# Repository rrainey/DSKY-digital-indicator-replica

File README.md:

# DSKY Digital Panel Replica

This is a scale functional replica of the Digital Indicator panel for the Apollo Guidance Computer. It is
designed to be part of a larger replica of the Display and Keyboard (DSKY) module of the AGC.

This project is composed of these component subfolders:

* **artwork** - artwork to be printed or silk-screened onto the glass/acrylic cover.

* **pcb** - KiCad 9 project for the controller PCB design.

* **firmware** - Arduino-based controller firmware.  This module is designed to be controlled via the USB serial interface.

* **hardware** - 3D-printable frame components designed using Fusion 360. STEP and Fusion source files available. Hardware models used in thie replica were derived from models that are part of in the [AGC Mechanical CAD project](https://github.com/rrainey/agc-mechanical-cad).

## Bill of Materials

|  Part                   | Grainger Part |   MFR Part  | QTY | Description |
|------------------------|:---------------:|-------------|:-----:|-------------|
|  M2.5-0.45 Brass Insert| [1GNL7](https://www.grainger.com/product/Heat-Set-Insert-M2-5-0-45-1GNL7?searchQuery=1GNL7&searchBar=true) |  TH-M25-SV-PK100 | 4 | Brass inserts (sold as 100 pack) |
|  M2.5 x 6mm Screw      | [6HB66](https://www.grainger.com/product/Machine-Screw-M2-5-Thread-6HB66) |  MPFD025060-100P1 | 4 | Machine screw: M2.5 Thread Size, 6 mm Lg, Steel, Zinc Plated, Flat, Phillips, Metric (sold as 100 pack) |
| Body                   | - | - | 1 | 3D Printable part |
| Retainer               | - | - | 1 | 3D Printable part |
| Light Guide            | - | - | 1 | CNC or 3D Printable part |
| PCB to Light Guide Adapter | - | - | 1 | 3D Printable part |
| Indicator face         | - | - | 1 | Paper Printable part |

Models for all printable parts are located in the hardware subfolder.

## Interfaces

* USB 2.0 Micro-B port
* J-LINK-compatible SWD debugging interface (10-pin header)
* Power: +3.3VDC via a 4-pin header (2.1A maximum (estimated; software limited to 0.5A))

## Printed Circuit Board

Summary below. You will find more detailed notes in the [./pcb folder](./pcb/PCB-NOTES.md).

As of March 2025, V7 of the PCB design is current. Gerber and component placement files -- all generated by KiCad 7, are included in this repository.  [PCBWay](https://pcbway.com) generously sponsored this version of the project. If you are building one of these boards, you should consider them for either PCB fabrication or full-up PCB assembly.

I often use a solder reflow oven in my shop. I used PCBWay for full PCBA services on this latest version, but with the earlier boards - I assembled them myself using a [two step process](https://www.instructables.com/Making-double-side-boards-in-reflow-oven/) to first reflow the back (LED) side using Sn63/Pb37 paste, then reflow the front side using a lower temperature solder paste (Bi57Sn42Ag1).  

## Painting

The original NASA drawings for all variants of this component, [1006387D for example,](https://archive.org/stream/apertureCardBox439Part2NARASW_images#page/n409/mode/1up) point to [this NASA paint specification [1008809-1]](https://archive.org/stream/apertureCardBox443NARASW_images#page/n504/mode/1up). It states [FED-STD 36231](http://federalstandard595.com/36231/) as the external color of the unit.  Good quality historial photos (examples [here](https://www.icollector.com/Apollo-CM-DSKY_i21861898) and [here](http://nassp.sourceforge.net/wiki/File:DSKY.jpg)) seem to imply a slightly different shade of gray, though. 

I may custom mix using Nazdar pigments, or I might simply use [an aircraft-grade epoxy premix](https://www.skygeek.com/deft-01-series-epoxy-topcoat-gray-36231-mil-prf-227750g.html) of FS36231. For now, I am simply using Krylon brand [Ultra Matte Finish - 4102 Misty Gray](https://www.google.com/search?q=Ultra+Matte+Finish+-+4102+Misty+Gray&rlz=1C1AFAB_enUS475US475&oq=Ultra+Matte+Finish+-+4102+Misty+Gray&aqs=chrome..69i57.432j0j7&sourceid=chrome&ie=UTF-8) paint.

## Credits and Related Projects

This project is inspired by work by Ben Krasnow creating a DSKY Electroluminescent Panel replica. You'll
find information about that project in [this Applied Science video](https://www.youtube.com/watch?v=Z2o_Sp2-aBo) by Ben. Like Ben's E/L display, this project is driven by an AT SAMD21 microcontroller chip; the same chip is used in the multiple Adafruit microcontroller boards, including the Adafruit Trinket M0.

## DSKY Digital Indicator License

Creative Commons Attribution/Share-Alike, all text above must be included in any redistribution. See license.txt for additional details.

## My Background

My name is Riley Rainey. I'm a software developer by profession. I spent a number of years building aerospace simulations as my day job.

## Getting Support

There's no official support available, but you can [leave comments or create an issue](https://github.com/rrainey/DSKY-digital-indicator-replica/issues) in this GitHub project.

This work is licensed under a [Creative Commons Attribution-ShareAlike 4.0 International License](http://creativecommons.org/licenses/by-sa/4.0/).

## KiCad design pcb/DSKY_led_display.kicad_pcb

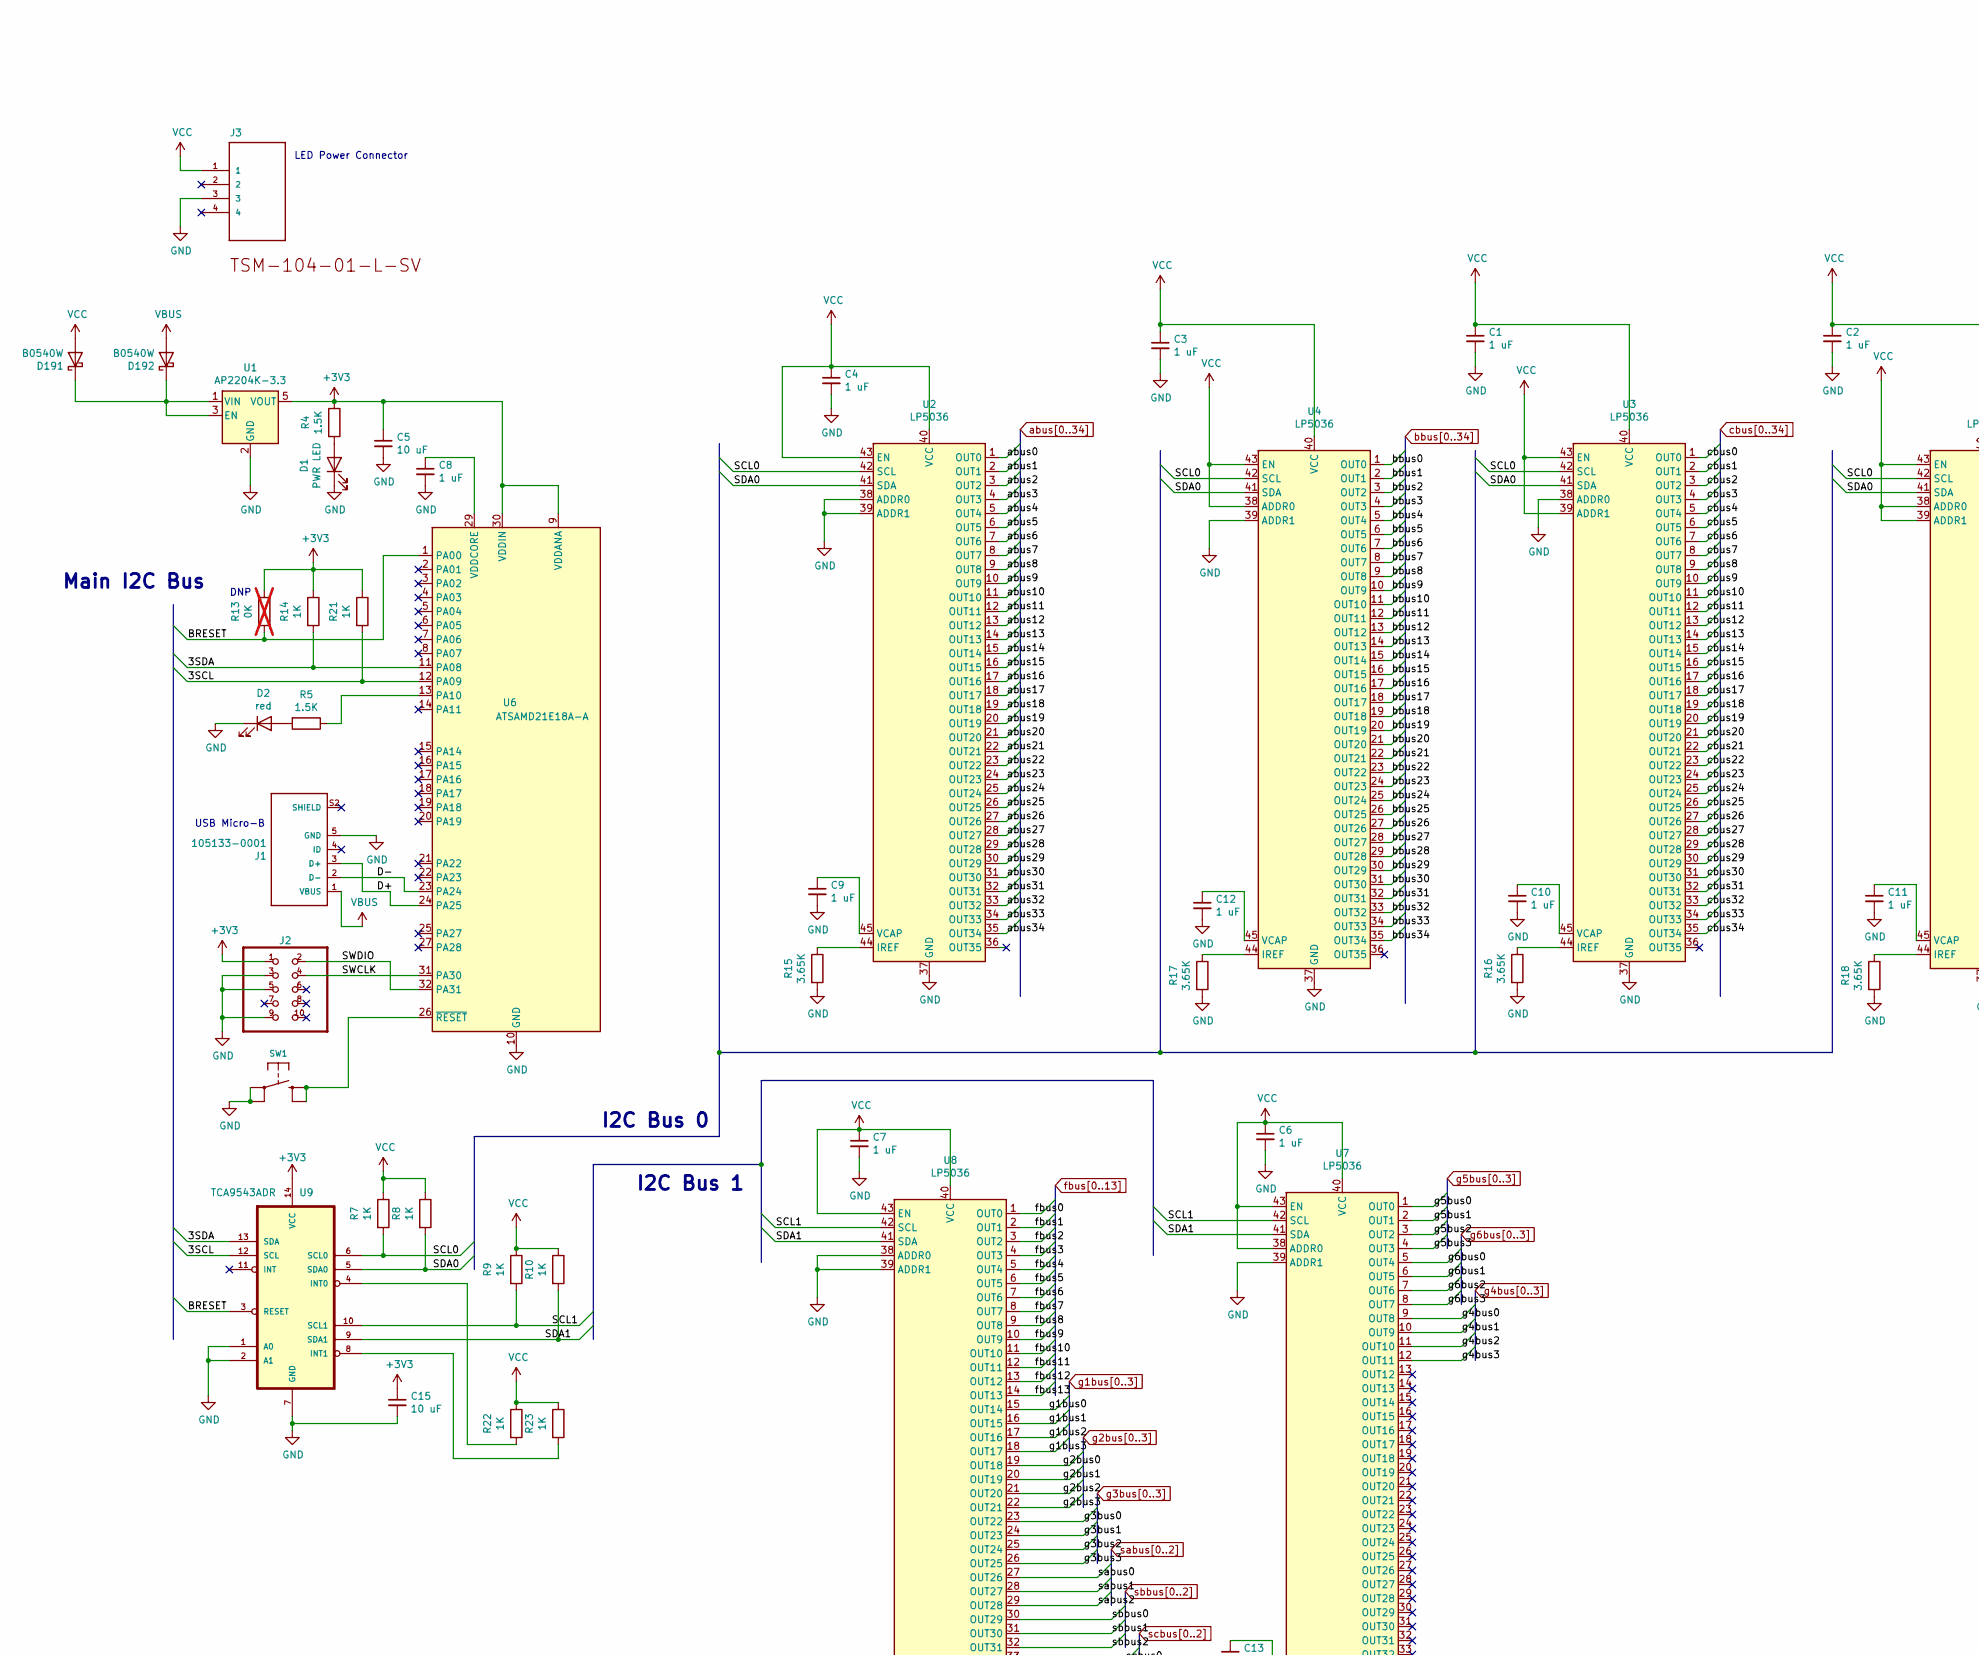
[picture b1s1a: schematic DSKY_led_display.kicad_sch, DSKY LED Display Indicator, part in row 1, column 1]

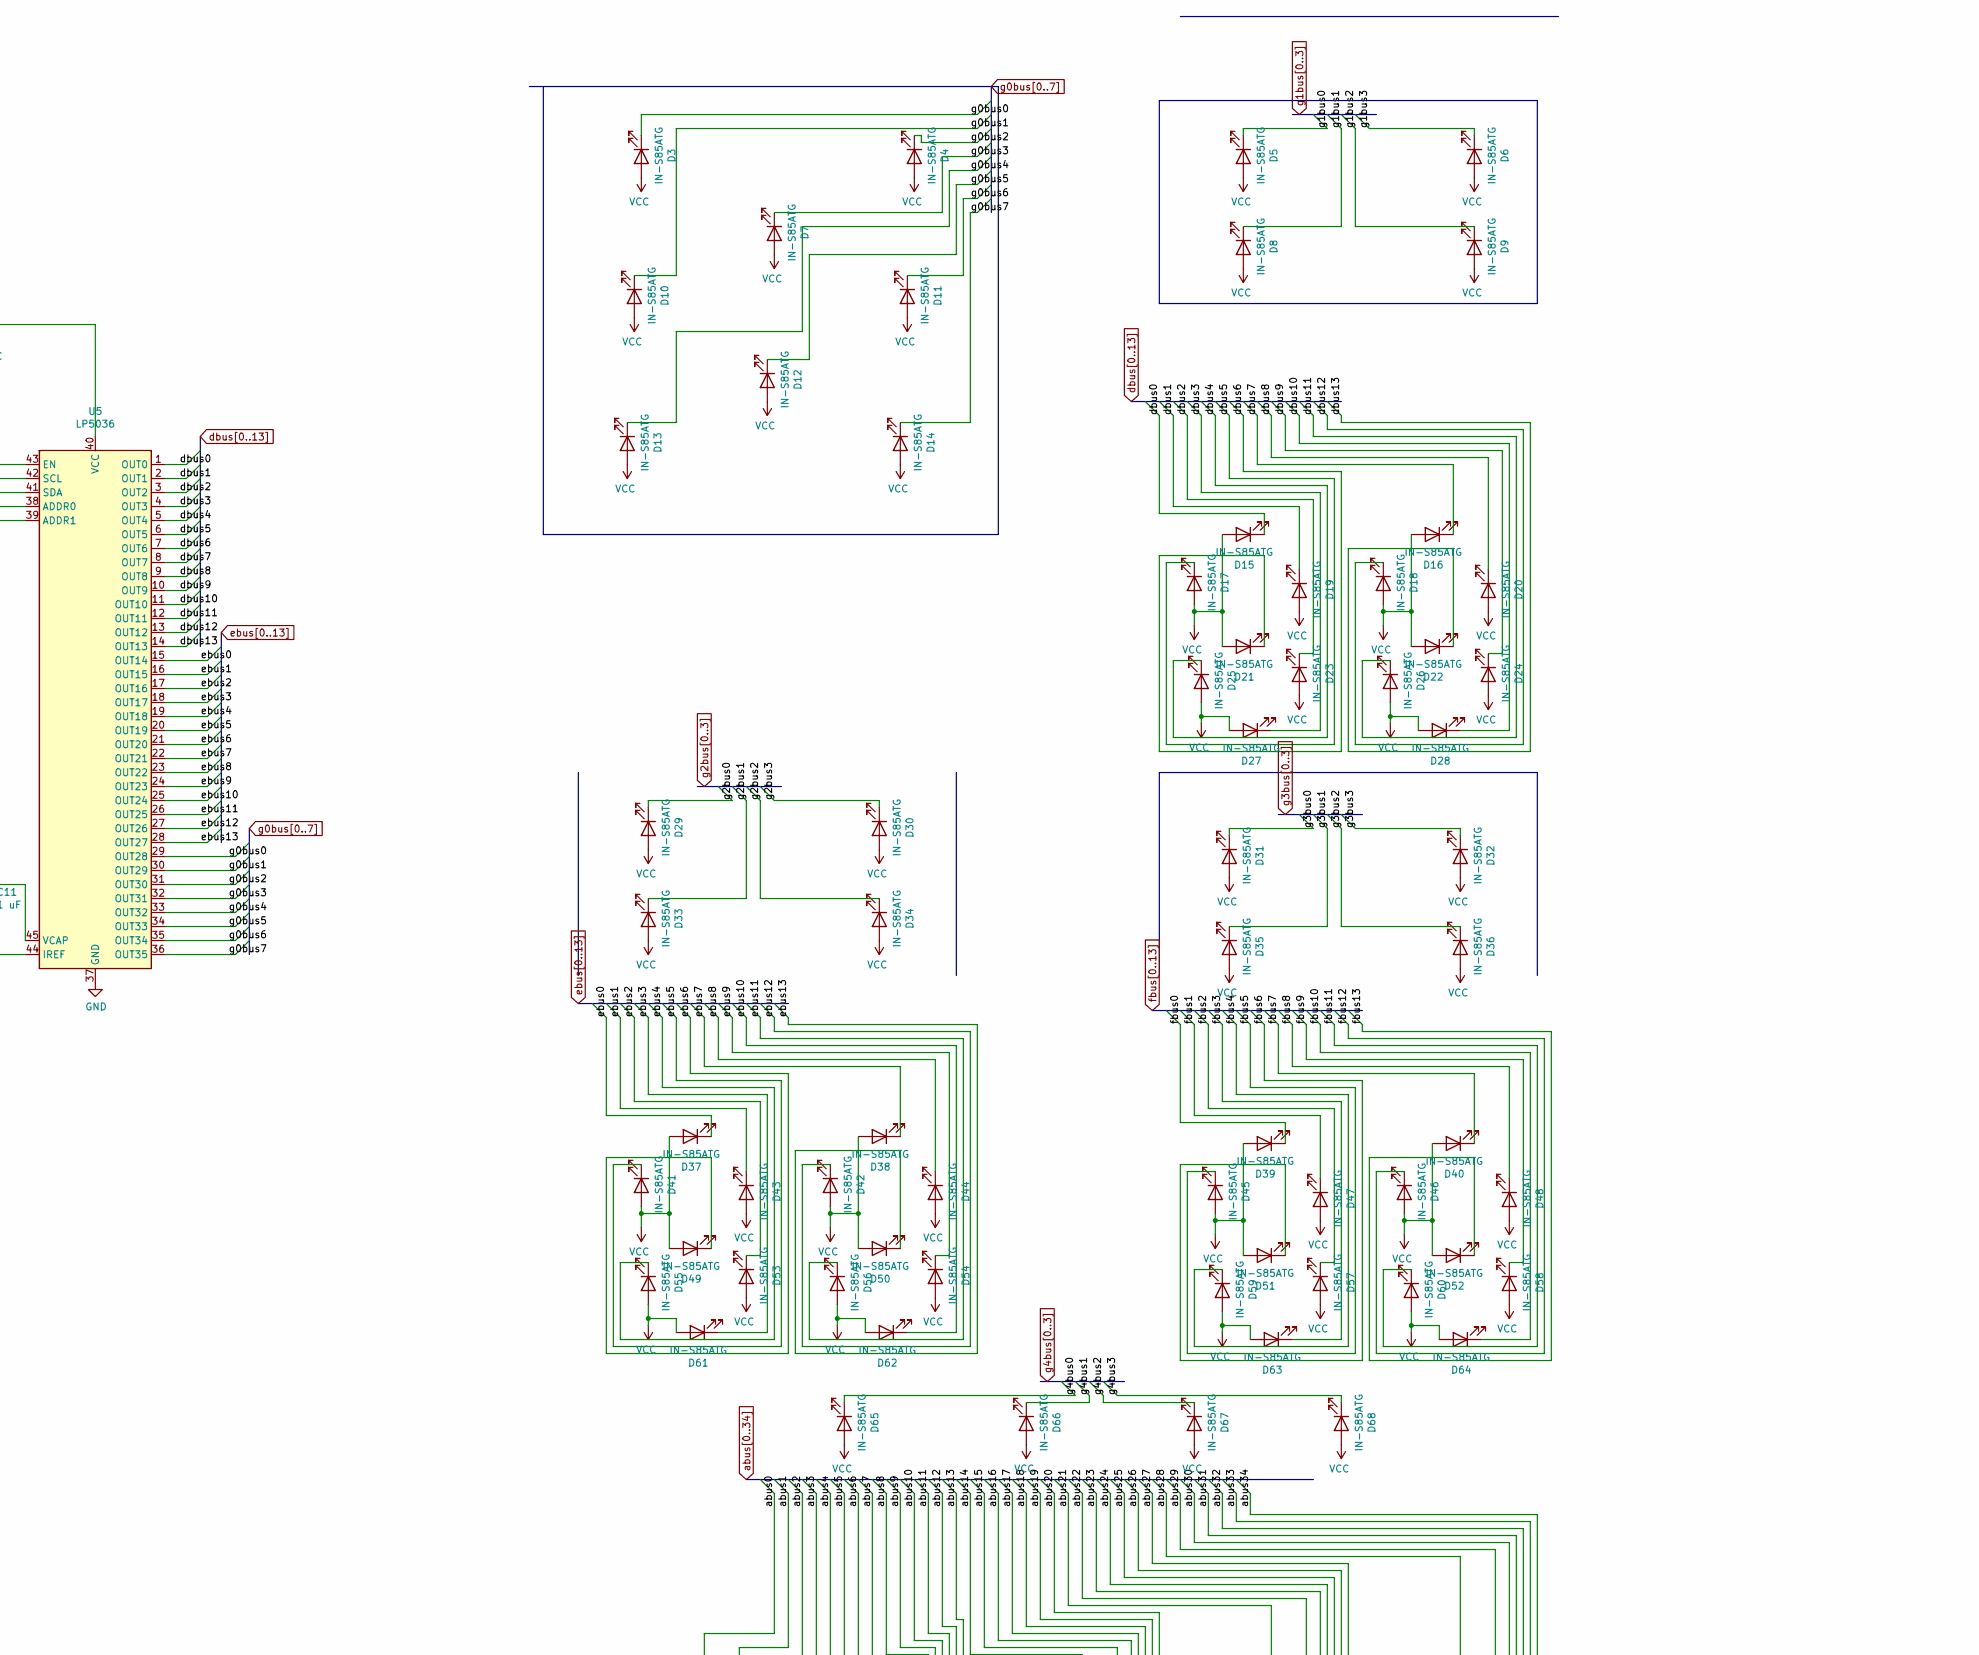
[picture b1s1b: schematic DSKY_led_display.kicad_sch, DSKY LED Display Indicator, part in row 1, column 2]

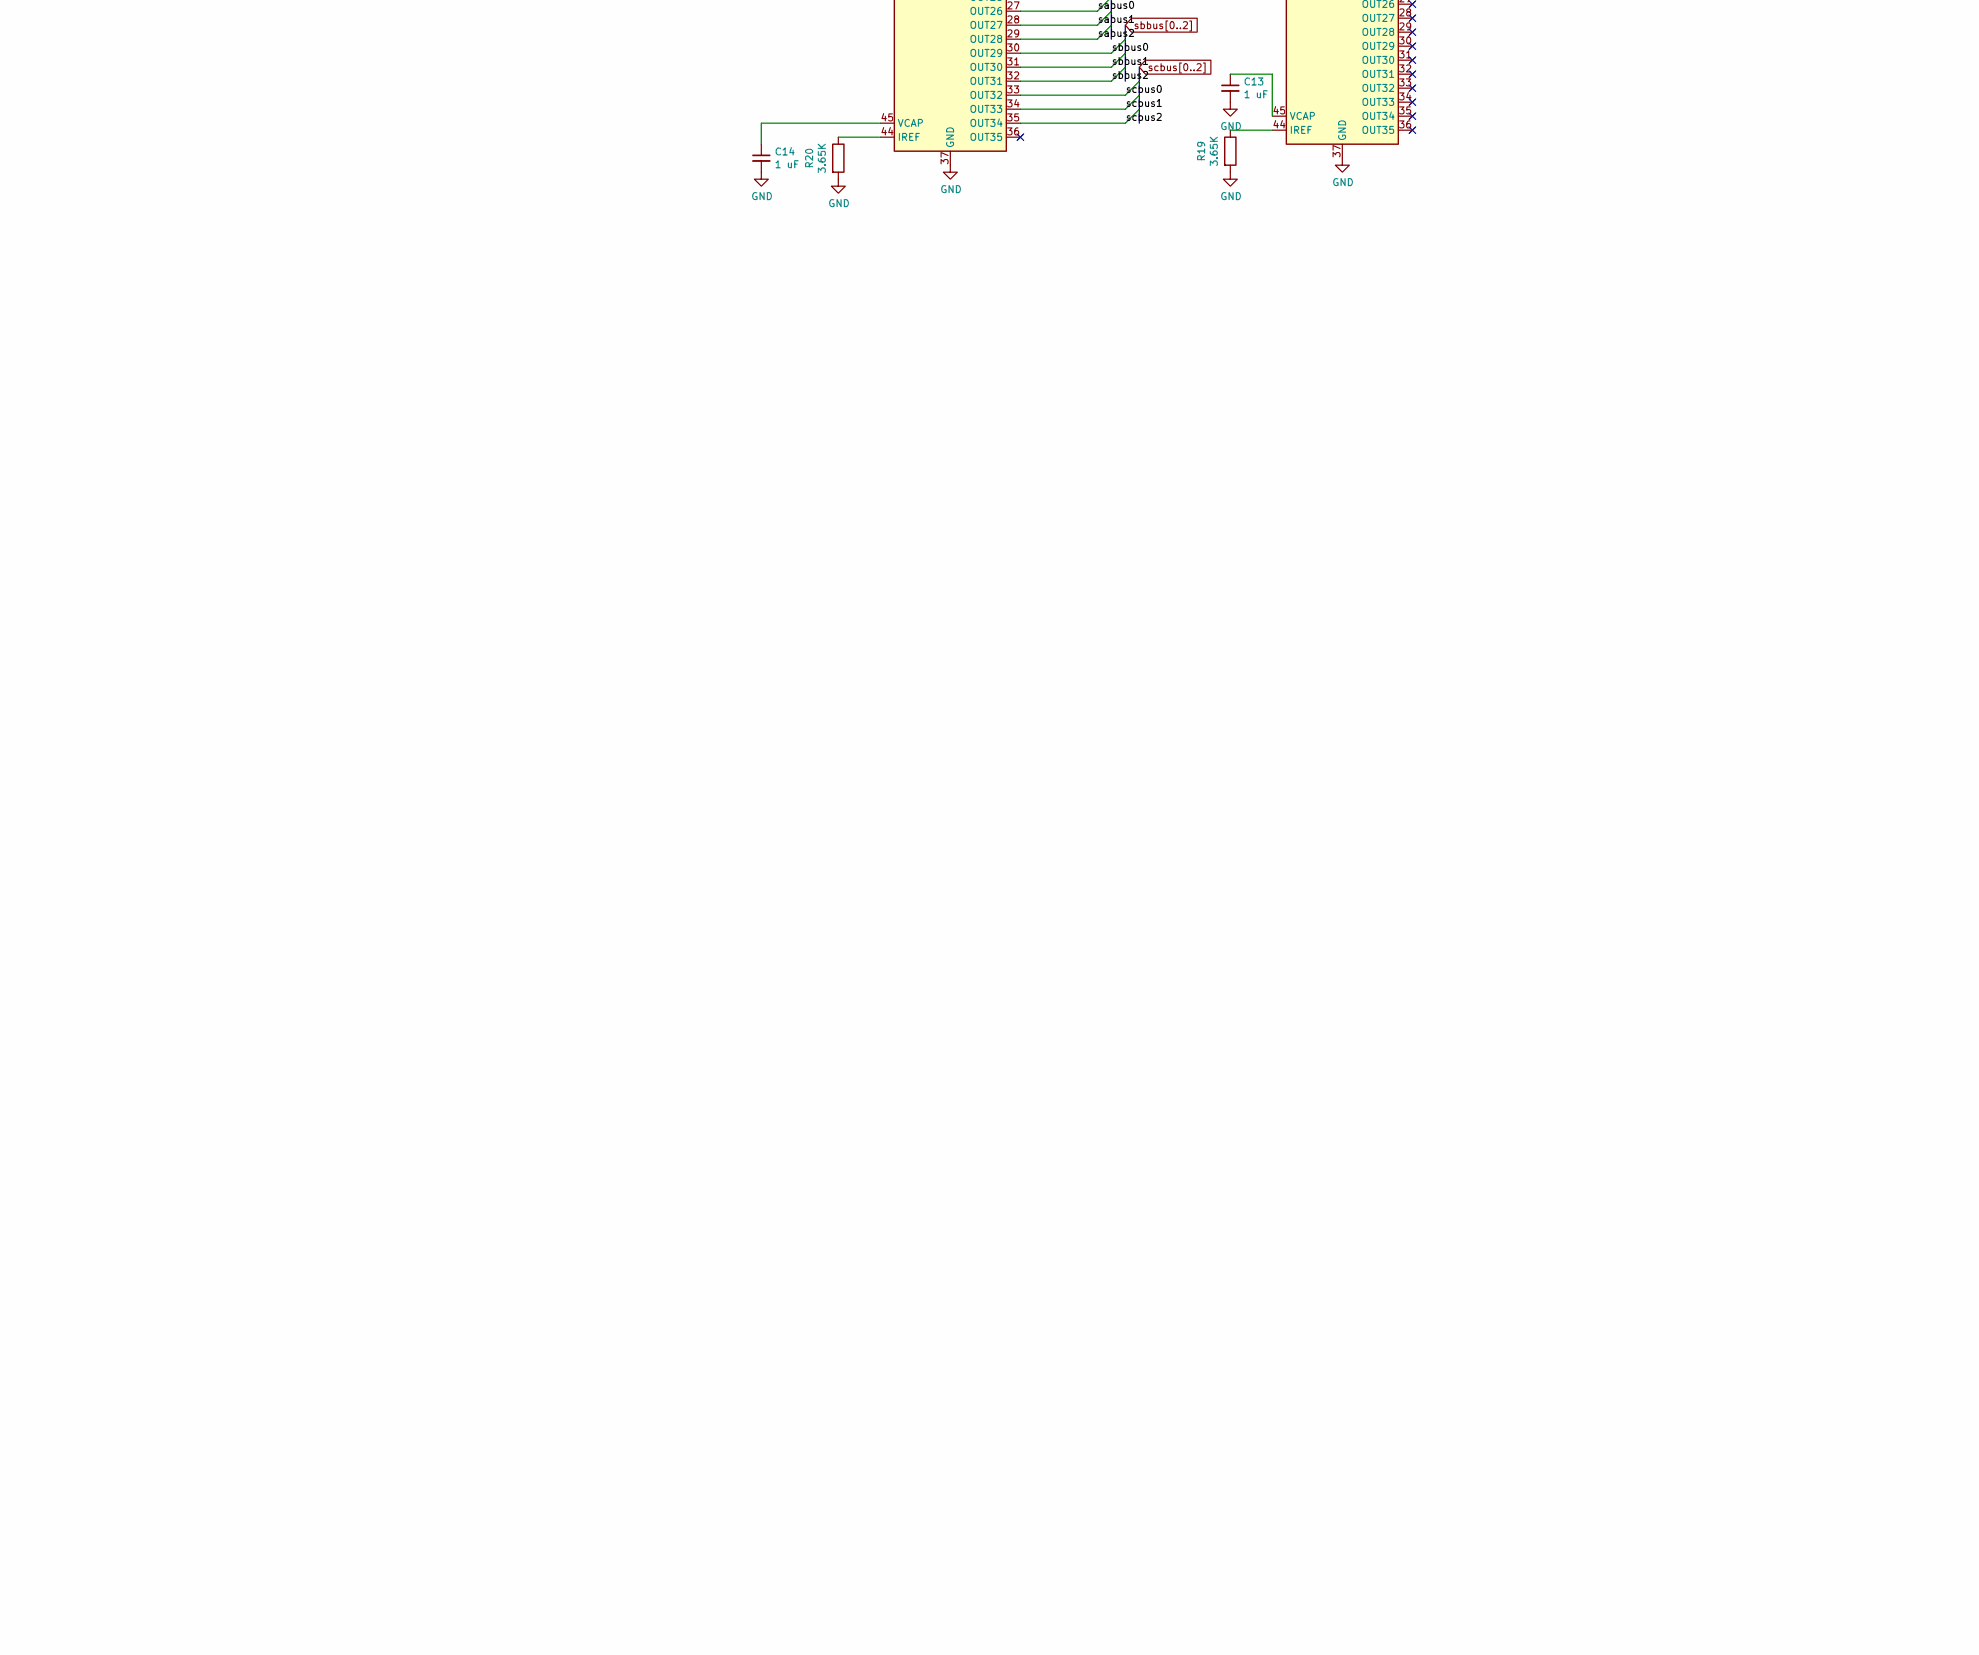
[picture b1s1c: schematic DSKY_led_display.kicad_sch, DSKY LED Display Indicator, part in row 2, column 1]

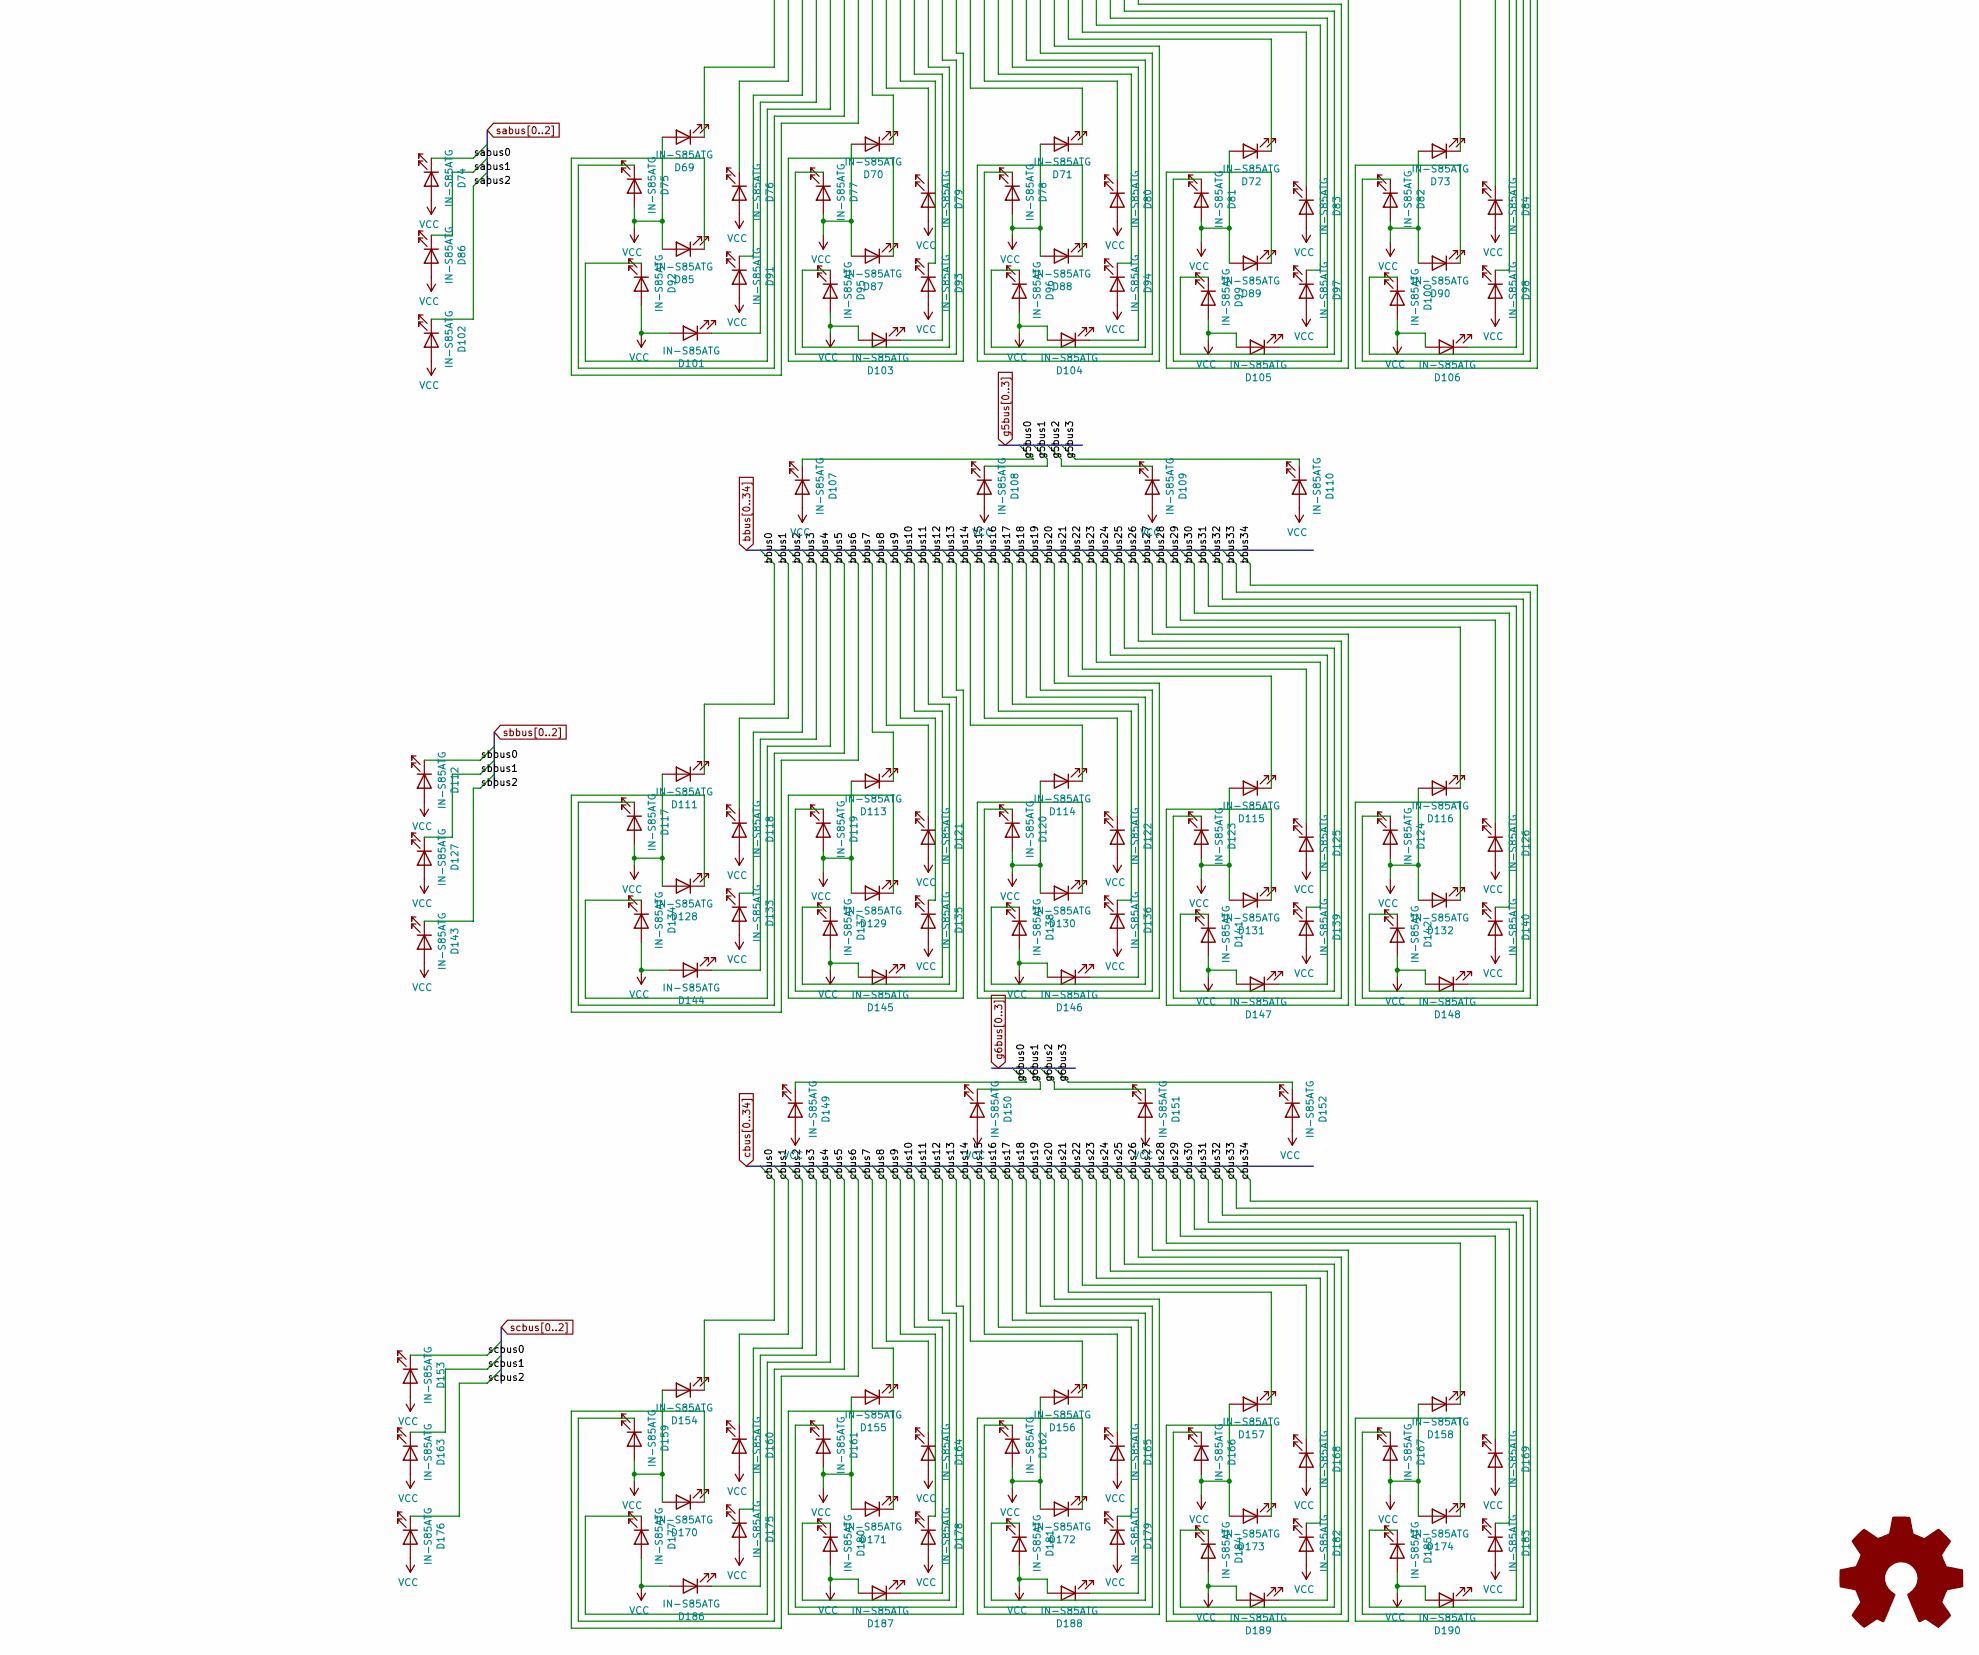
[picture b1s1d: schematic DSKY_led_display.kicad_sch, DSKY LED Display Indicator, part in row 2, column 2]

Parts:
C1, C2, C3, C4, C6, C7, C8, C9, C10, C11, C12, C13, C14: 1 uF; C_0603_1608Metric; Digi-Key_PN 399-C0603C105K3RAC7411CT-ND
C5, C15: 10 uF; C_0603_1608Metric; Digi-Key_PN 311-3494-1-ND
D1: PWR LED; LED_0603_1608Metric; Digi-Key_PN 160-1183-1-ND
D2: red; LED_0603_1608Metric; Digi-Key_PN 732-4978-1-ND
D3, D4, D5, D6, D7, D8, D9, D10, D11, D12, D13, D14, D15, D16, D17, D18, D19, D20, D21, D22, D23, D24, D25, D26, D27, D28, D29, D30, D31, D32, D33, D34, D35, D36, D37, D38, D39, D40, D41, D42, D43, D44, D45, D46, D47, D48, D49, D50, D51, D52, D53, D54, D55, D56, D57, D58, D59, D60, D61, D62, D63, D64, D65, D66, D67, D68, D69, D70, D71, D72, D73, D74, D75, D76, D77, D78, D79, D80, D81, D82, D83, D84, D85, D86, D87, D88, D89, D90, D91, D92, D93, D94, D95, D96, D97, D98, D99, D100, D101, D102, D103, D104, D105, D106, D107, D108, D109, D110, D111, D112, D113, D114, D115, D116, D117, D118, D119, D120, D121, D122, D123, D124, D125, D126, D127, D128, D129, D130, D131, D132, D133, D134, D135, D136, D137, D138, D139, D140, D141, D142, D143, D144, D145, D146, D147, D148, D149, D150, D151, D152, D153, D154, D155, D156, D157, D158, D159, D160, D161, D162, D163, D164, D165, D166, D167, D168, D169, D170, D171, D172, D173, D174, D175, D176, D177, D178, D179, D180, D181, D182, D183, D184, D185, D186, D187, D188, D189, D190: IN-S85ATG; LED_0805_2012Metric; Digi-Key_PN 1830-1079-1-ND
D191, D192: B0540W; D_SOD-123F; Digi-Key_PN 1801-B0540WTR-ND
J1: 105133-0001; MOLEX_105133-0001; Digi-Key_PN WM9734CT-ND
J2: 3221-10-0300-00-TR; Digi-Key_PN 1175-2649-1-ND
J3: TSM-104-01-L-SV; Digi-Key_PN SAM13287CT-ND
R4, R5: 1.5K; R_0603_1608Metric; Digi-Key_PN 541-1781-1-ND
R7, R8, R9, R10, R14, R21, R22, R23: 1K; R_0603_1608Metric; Digi-Key_PN 541-1.0KGCT-ND
R13: 0K; R_0603_1608Metric; not fitted
R15, R16, R17, R18, R19, R20: 3.65K; R_0603_1608Metric; Digi-Key_PN 541-3.65KSCT-ND
SW1: KMR241NG; BTN_KMR2_4.6X2.8; Digi-Key_PN CKN10247TR-ND
U1: AP2204K-3.3; SOT-23-5; Digi-Key_PN AP2204K-3.3TRG1DICT-ND
U2, U3, U4, U5, U7, U8: LP5036; VQFN-46-1EP_5x6mm_P0.4mm_EP2.8x3.8mm; Digi-Key_PN 296-LP5036RJVRCT-ND
U6: ATSAMD21E18A-A; TQFP-32_7x7mm_P0.8mm; Digi-Key_PN ATSAMD21E18A-AU-ND
U9: TCA9543ADR; SOIC-14_3.9x8.7mm_P1.27mm

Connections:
+3V3: C5.1, C15.1, J2.1, R4.1, R13.1, R14.1, R21.1, U1.5 (VOUT), U6.9 (VDDANA), U6.30 (VDDIN), U9.14 (VCC)
/3SCL: R21.2, U6.12 (PA09), U9.12 (SCL)
/3SDA: R14.2, U6.11 (PA08), U9.13 (SDA)
/BRESET: R13.2, U6.1 (PA00), U9.3 (RESET)
/D+: J1.3 (D+), U6.24 (PA25)
/D-: J1.2 (D-), U6.23 (PA24)
/SCL0: R7.2, U2.42 (SCL), U3.42 (SCL), U4.42 (SCL), U5.42 (SCL), U9.6 (SCL0)
/SCL1: R9.2, U7.42 (SCL), U8.42 (SCL), U9.10 (SCL1)
/SDA0: R8.2, U2.41 (SDA), U3.41 (SDA), U4.41 (SDA), U5.41 (SDA), U9.5 (SDA0)
/SDA1: R10.2, U7.41 (SDA), U8.41 (SDA), U9.9 (SDA1)
/SWCLK: J2.4, U6.31 (PA30)
/SWDIO: J2.2, U6.32 (PA31)
GND: C1.2, C2.2, C3.2, C4.2, C5.2, C6.2, C7.2, C8.2, C9.2, C10.2, C11.2, C12.2, C13.2, C14.2, C15.2, D1.1 (K), D2.1 (K), J1.5 (GND), J2.3, J2.5, J2.9, J3.3, R15.2, R16.2, R17.2, R18.2, R19.2, R20.2, SW1.A, SW1.A' (P1), U1.2 (GND), U2.37 (GND), U2.38 (ADDR0), U2.39 (ADDR1), U2.46 (GND), U2.47 (GND), U3.37 (GND), U3.38 (ADDR0), U3.46 (GND), U3.47 (GND), U4.37 (GND), U4.39 (ADDR1), U4.46 (GND), U4.47 (GND), U5.37 (GND), U5.46 (GND), U5.47 (GND), U6.10 (GND), U6.28 (GND), U7.37 (GND), U7.39 (ADDR1), U7.46 (GND), U7.47 (GND), U8.37 (GND), U8.38 (ADDR0), U8.39 (ADDR1), U8.46 (GND), U8.47 (GND), U9.1 (A0), U9.2 (A1), U9.7 (GND)
unnamed: D1.2 (A), R4.2
unnamed: D2.2 (A), R5.2
unnamed: D191.1 (K), D192.1 (K), U1.1 (VIN), U1.3 (EN)
unnamed: SW1.B (S), SW1.B' (S1), U6.26 (~RESET)
unnamed: R15.1, U2.44 (IREF)
unnamed: C9.1, U2.45 (VCAP)
unnamed: R16.1, U3.44 (IREF)
unnamed: C10.1, U3.45 (VCAP)
unnamed: R17.1, U4.44 (IREF)
unnamed: C12.1, U4.45 (VCAP)
unnamed: R18.1, U5.44 (IREF)
unnamed: C11.1, U5.45 (VCAP)
unnamed: R5.1, U6.13 (PA10)
unnamed: C8.1, U6.29 (VDDCORE)
unnamed: R19.1, U7.44 (IREF)
unnamed: C13.1, U7.45 (VCAP)
unnamed: R20.1, U8.44 (IREF)
unnamed: C14.1, U8.45 (VCAP)
unnamed: R22.2, U9.4 (INT0)
unnamed: R23.2, U9.8 (INT1)
VBUS: D192.2 (A), J1.1 (VBUS)
VCC: C1.1, C2.1, C3.1, C4.1, C6.1, C7.1, D3.2 (A), D4.2 (A), D5.2 (A), D6.2 (A), D7.2 (A), D8.2 (A), D9.2 (A), D10.2 (A), D11.2 (A), D12.2 (A), D13.2 (A), D14.2 (A), D15.2 (A), D16.2 (A), D17.2 (A), D18.2 (A), D19.2 (A), D20.2 (A), D21.2 (A), D22.2 (A), D23.2 (A), D24.2 (A), D25.2 (A), D26.2 (A), D27.2 (A), D28.2 (A), D29.2 (A), D30.2 (A), D31.2 (A), D32.2 (A), D33.2 (A), D34.2 (A), D35.2 (A), D36.2 (A), D37.2 (A), D38.2 (A), D39.2 (A), D40.2 (A), D41.2 (A), D42.2 (A), D43.2 (A), D44.2 (A), D45.2 (A), D46.2 (A), D47.2 (A), D48.2 (A), D49.2 (A), D50.2 (A), D51.2 (A), D52.2 (A), D53.2 (A), D54.2 (A), D55.2 (A), D56.2 (A), D57.2 (A), D58.2 (A), D59.2 (A), D60.2 (A), D61.2 (A), D62.2 (A), D63.2 (A), D64.2 (A), D65.2 (A), D66.2 (A), D67.2 (A), D68.2 (A), D69.2 (A), D70.2 (A), D71.2 (A), D72.2 (A), D73.2 (A), D74.2 (A), D75.2 (A), D76.2 (A), D77.2 (A), D78.2 (A), D79.2 (A), D80.2 (A), D81.2 (A), D82.2 (A), D83.2 (A), D84.2 (A), D85.2 (A), D86.2 (A), D87.2 (A), D88.2 (A), D89.2 (A), D90.2 (A), D91.2 (A), D92.2 (A), D93.2 (A), D94.2 (A), D95.2 (A), D96.2 (A), D97.2 (A), D98.2 (A), D99.2 (A), D100.2 (A), D101.2 (A), D102.2 (A), D103.2 (A), D104.2 (A), D105.2 (A), D106.2 (A), D107.2 (A), D108.2 (A), D109.2 (A), D110.2 (A), D111.2 (A), D112.2 (A), D113.2 (A), D114.2 (A), D115.2 (A), D116.2 (A), D117.2 (A), D118.2 (A), D119.2 (A), D120.2 (A), D121.2 (A), D122.2 (A), D123.2 (A), D124.2 (A), D125.2 (A), D126.2 (A), D127.2 (A), D128.2 (A), D129.2 (A), D130.2 (A), D131.2 (A), D132.2 (A), D133.2 (A), D134.2 (A), D135.2 (A), D136.2 (A), D137.2 (A), D138.2 (A), D139.2 (A), D140.2 (A), D141.2 (A), D142.2 (A), D143.2 (A), D144.2 (A), D145.2 (A), D146.2 (A), D147.2 (A), D148.2 (A), D149.2 (A), D150.2 (A), D151.2 (A), D152.2 (A), D153.2 (A), D154.2 (A), D155.2 (A), D156.2 (A), D157.2 (A), D158.2 (A), D159.2 (A), D160.2 (A), D161.2 (A), D162.2 (A), D163.2 (A), D164.2 (A), D165.2 (A), D166.2 (A), D167.2 (A), D168.2 (A), D169.2 (A), D170.2 (A), D171.2 (A), D172.2 (A), D173.2 (A), D174.2 (A), D175.2 (A), D176.2 (A), D177.2 (A), D178.2 (A), D179.2 (A), D180.2 (A), D181.2 (A), D182.2 (A), D183.2 (A), D184.2 (A), D185.2 (A), D186.2 (A), D187.2 (A), D188.2 (A), D189.2 (A), D190.2 (A), D191.2 (A), J3.1, R7.1, R8.1, R9.1, R10.1, R22.1, R23.1, U2.40 (VCC), U2.43 (EN), U3.39 (ADDR1), U3.40 (VCC), U3.43 (EN), U4.38 (ADDR0), U4.40 (VCC), U4.43 (EN), U5.38 (ADDR0), U5.39 (ADDR1), U5.40 (VCC), U5.43 (EN), U7.38 (ADDR0), U7.40 (VCC), U7.43 (EN), U8.40 (VCC), U8.43 (EN)
abus0: D69.1 (K), U2.1 (OUT0)
abus1: D76.1 (K), U2.2 (OUT1)
abus2: D91.1 (K), U2.3 (OUT2)
abus3: D101.1 (K), U2.4 (OUT3)
abus4: D92.1 (K), U2.5 (OUT4)
abus5: D75.1 (K), U2.6 (OUT5)
abus6: D85.1 (K), U2.7 (OUT6)
abus7: D70.1 (K), U2.8 (OUT7)
abus8: D79.1 (K), U2.9 (OUT8)
abus9: D93.1 (K), U2.10 (OUT9)
abus10: D103.1 (K), U2.11 (OUT10)
abus11: D95.1 (K), U2.12 (OUT11)
abus12: D77.1 (K), U2.13 (OUT12)
abus13: D87.1 (K), U2.14 (OUT13)
abus14: D71.1 (K), U2.15 (OUT14)
abus15: D80.1 (K), U2.16 (OUT15)
abus16: D94.1 (K), U2.17 (OUT16)
abus17: D104.1 (K), U2.18 (OUT17)
abus18: D96.1 (K), U2.19 (OUT18)
abus19: D78.1 (K), U2.20 (OUT19)
abus20: D88.1 (K), U2.21 (OUT20)
abus21: D72.1 (K), U2.22 (OUT21)
abus22: D83.1 (K), U2.23 (OUT22)
abus23: D97.1 (K), U2.24 (OUT23)
abus24: D105.1 (K), U2.25 (OUT24)
abus25: D99.1 (K), U2.26 (OUT25)
abus26: D81.1 (K), U2.27 (OUT26)
abus27: D89.1 (K), U2.28 (OUT27)
abus28: D73.1 (K), U2.29 (OUT28)
abus29: D84.1 (K), U2.30 (OUT29)
abus30: D98.1 (K), U2.31 (OUT30)
abus31: D106.1 (K), U2.32 (OUT31)
abus32: D100.1 (K), U2.33 (OUT32)
abus33: D82.1 (K), U2.34 (OUT33)
abus34: D90.1 (K), U2.35 (OUT34)
bbus0: D111.1 (K), U4.1 (OUT0)
bbus1: D118.1 (K), U4.2 (OUT1)
bbus2: D133.1 (K), U4.3 (OUT2)
bbus3: D144.1 (K), U4.4 (OUT3)
bbus4: D134.1 (K), U4.5 (OUT4)
bbus5: D117.1 (K), U4.6 (OUT5)
bbus6: D128.1 (K), U4.7 (OUT6)
bbus7: D113.1 (K), U4.8 (OUT7)
bbus8: D121.1 (K), U4.9 (OUT8)
bbus9: D135.1 (K), U4.10 (OUT9)
bbus10: D145.1 (K), U4.11 (OUT10)
bbus11: D137.1 (K), U4.12 (OUT11)
bbus12: D119.1 (K), U4.13 (OUT12)
bbus13: D129.1 (K), U4.14 (OUT13)
bbus14: D114.1 (K), U4.15 (OUT14)
bbus15: D122.1 (K), U4.16 (OUT15)
bbus16: D136.1 (K), U4.17 (OUT16)
bbus17: D146.1 (K), U4.18 (OUT17)
bbus18: D138.1 (K), U4.19 (OUT18)
bbus19: D120.1 (K), U4.20 (OUT19)
bbus20: D130.1 (K), U4.21 (OUT20)
bbus21: D115.1 (K), U4.22 (OUT21)
bbus22: D125.1 (K), U4.23 (OUT22)
bbus23: D139.1 (K), U4.24 (OUT23)
bbus24: D147.1 (K), U4.25 (OUT24)
bbus25: D141.1 (K), U4.26 (OUT25)
bbus26: D123.1 (K), U4.27 (OUT26)
bbus27: D131.1 (K), U4.28 (OUT27)
bbus28: D116.1 (K), U4.29 (OUT28)
bbus29: D126.1 (K), U4.30 (OUT29)
bbus30: D140.1 (K), U4.31 (OUT30)
bbus31: D148.1 (K), U4.32 (OUT31)
bbus32: D142.1 (K), U4.33 (OUT32)
bbus33: D124.1 (K), U4.34 (OUT33)
bbus34: D132.1 (K), U4.35 (OUT34)
cbus0: D154.1 (K), U3.1 (OUT0)
cbus1: D160.1 (K), U3.2 (OUT1)
cbus2: D175.1 (K), U3.3 (OUT2)
cbus3: D186.1 (K), U3.4 (OUT3)
cbus4: D177.1 (K), U3.5 (OUT4)
cbus5: D159.1 (K), U3.6 (OUT5)
cbus6: D170.1 (K), U3.7 (OUT6)
cbus7: D155.1 (K), U3.8 (OUT7)
cbus8: D164.1 (K), U3.9 (OUT8)
cbus9: D178.1 (K), U3.10 (OUT9)
cbus10: D187.1 (K), U3.11 (OUT10)
cbus11: D180.1 (K), U3.12 (OUT11)
cbus12: D161.1 (K), U3.13 (OUT12)
cbus13: D171.1 (K), U3.14 (OUT13)
cbus14: D156.1 (K), U3.15 (OUT14)
cbus15: D165.1 (K), U3.16 (OUT15)
cbus16: D179.1 (K), U3.17 (OUT16)
cbus17: D188.1 (K), U3.18 (OUT17)
cbus18: D181.1 (K), U3.19 (OUT18)
cbus19: D162.1 (K), U3.20 (OUT19)
cbus20: D172.1 (K), U3.21 (OUT20)
cbus21: D157.1 (K), U3.22 (OUT21)
cbus22: D168.1 (K), U3.23 (OUT22)
cbus23: D182.1 (K), U3.24 (OUT23)
cbus24: D189.1 (K), U3.25 (OUT24)
cbus25: D184.1 (K), U3.26 (OUT25)
cbus26: D166.1 (K), U3.27 (OUT26)
cbus27: D173.1 (K), U3.28 (OUT27)
cbus28: D158.1 (K), U3.29 (OUT28)
cbus29: D169.1 (K), U3.30 (OUT29)
cbus30: D183.1 (K), U3.31 (OUT30)
cbus31: D190.1 (K), U3.32 (OUT31)
cbus32: D185.1 (K), U3.33 (OUT32)
cbus33: D167.1 (K), U3.34 (OUT33)
cbus34: D174.1 (K), U3.35 (OUT34)
dbus0: D15.1 (K), U5.1 (OUT0)
dbus1: D19.1 (K), U5.2 (OUT1)
dbus2: D23.1 (K), U5.3 (OUT2)
dbus3: D27.1 (K), U5.4 (OUT3)
dbus4: D25.1 (K), U5.5 (OUT4)
dbus5: D17.1 (K), U5.6 (OUT5)
dbus6: D21.1 (K), U5.7 (OUT6)
dbus7: D16.1 (K), U5.8 (OUT7)
dbus8: D20.1 (K), U5.9 (OUT8)
dbus9: D24.1 (K), U5.10 (OUT9)
dbus10: D28.1 (K), U5.11 (OUT10)
dbus11: D26.1 (K), U5.12 (OUT11)
dbus12: D18.1 (K), U5.13 (OUT12)
dbus13: D22.1 (K), U5.14 (OUT13)
ebus0: D37.1 (K), U5.15 (OUT14)
ebus1: D43.1 (K), U5.16 (OUT15)
ebus2: D53.1 (K), U5.17 (OUT16)
ebus3: D61.1 (K), U5.18 (OUT17)
ebus4: D55.1 (K), U5.19 (OUT18)
ebus5: D41.1 (K), U5.20 (OUT19)
ebus6: D49.1 (K), U5.21 (OUT20)
ebus7: D38.1 (K), U5.22 (OUT21)
ebus8: D44.1 (K), U5.23 (OUT22)
ebus9: D54.1 (K), U5.24 (OUT23)
ebus10: D62.1 (K), U5.25 (OUT24)
ebus11: D56.1 (K), U5.26 (OUT25)
ebus12: D42.1 (K), U5.27 (OUT26)
ebus13: D50.1 (K), U5.28 (OUT27)
fbus0: D39.1 (K), U8.1 (OUT0)
fbus1: D47.1 (K), U8.2 (OUT1)
fbus2: D57.1 (K), U8.3 (OUT2)
fbus3: D63.1 (K), U8.4 (OUT3)
fbus4: D59.1 (K), U8.5 (OUT4)
fbus5: D45.1 (K), U8.6 (OUT5)
fbus6: D51.1 (K), U8.7 (OUT6)
fbus7: D40.1 (K), U8.8 (OUT7)
fbus8: D48.1 (K), U8.9 (OUT8)
fbus9: D58.1 (K), U8.10 (OUT9)
fbus10: D64.1 (K), U8.11 (OUT10)
fbus11: D60.1 (K), U8.12 (OUT11)
fbus12: D46.1 (K), U8.13 (OUT12)
fbus13: D52.1 (K), U8.14 (OUT13)
g0bus0: D3.1 (K), U5.29 (OUT28)
g0bus1: D10.1 (K), U5.30 (OUT29)
g0bus2: D4.1 (K), U5.31 (OUT30)
g0bus3: D7.1 (K), U5.32 (OUT31)
g0bus4: D13.1 (K), U5.33 (OUT32)
g0bus5: D12.1 (K), U5.34 (OUT33)
g0bus6: D11.1 (K), U5.35 (OUT34)
g0bus7: D14.1 (K), U5.36 (OUT35)
g1bus0: D5.1 (K), U8.15 (OUT14)
g1bus1: D8.1 (K), U8.16 (OUT15)
g1bus2: D9.1 (K), U8.17 (OUT16)
g1bus3: D6.1 (K), U8.18 (OUT17)
g2bus0: D29.1 (K), U8.19 (OUT18)
g2bus1: D33.1 (K), U8.20 (OUT19)
g2bus2: D34.1 (K), U8.21 (OUT20)
g2bus3: D30.1 (K), U8.22 (OUT21)
g3bus0: D31.1 (K), U8.23 (OUT22)
g3bus1: D35.1 (K), U8.24 (OUT23)
g3bus2: D36.1 (K), U8.25 (OUT24)
g3bus3: D32.1 (K), U8.26 (OUT25)
g4bus0: D65.1 (K), U7.9 (OUT8)
g4bus1: D66.1 (K), U7.10 (OUT9)
g4bus2: D67.1 (K), U7.11 (OUT10)
g4bus3: D68.1 (K), U7.12 (OUT11)
g5bus0: D107.1 (K), U7.1 (OUT0)
g5bus1: D108.1 (K), U7.2 (OUT1)
g5bus2: D109.1 (K), U7.3 (OUT2)
g5bus3: D110.1 (K), U7.4 (OUT3)
g6bus0: D149.1 (K), U7.5 (OUT4)
g6bus1: D150.1 (K), U7.6 (OUT5)
g6bus2: D151.1 (K), U7.7 (OUT6)
g6bus3: D152.1 (K), U7.8 (OUT7)
sabus0: D74.1 (K), U8.27 (OUT26)
sabus1: D86.1 (K), U8.28 (OUT27)
sabus2: D102.1 (K), U8.29 (OUT28)
sbbus0: D112.1 (K), U8.30 (OUT29)
sbbus1: D127.1 (K), U8.31 (OUT30)
sbbus2: D143.1 (K), U8.32 (OUT31)
scbus0: D153.1 (K), U8.33 (OUT32)
scbus1: D163.1 (K), U8.34 (OUT33)
scbus2: D176.1 (K), U8.35 (OUT34)

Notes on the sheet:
I2C Bus 1
LED Power Connector
Main I2C Bus
USB Micro-B
I2C Bus 0
DNP

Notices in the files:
README.md:
CC BY-SA 4.0
